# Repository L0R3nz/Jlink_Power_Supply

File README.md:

# Jlink_Power_Supply

## Project background
It's a simple project which help me in my work. I face a problem that I have to supply micro with 3V3.
J-Link allow us to supply only with 5V so I design this board to solve that problem. 

## Schematic
Schematic is very simple but if you need you can find it [here](Docs/Schematic.pdf)

## Gerber Files
Complite package ready for production you can find [here](https://github.com/L0R3nz/Jlink_Power_Supply/releases/latest)

## 3D Render

## Real photos

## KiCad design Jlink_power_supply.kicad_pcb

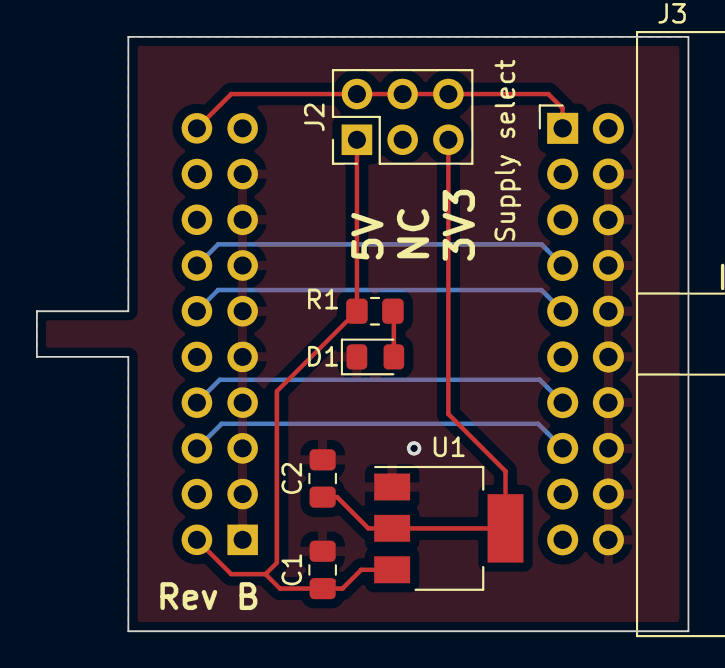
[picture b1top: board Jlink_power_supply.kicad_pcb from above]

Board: 2 copper layers, 36.2 x 33.0 mm, 8 parts (1 on the bottom side), 9 nets.

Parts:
C1, C2: 10uF; C_0805_2012Metric_Pad1.18x1.45mm_HandSolder
D1: LED_0805_2012Metric_Pad1.15x1.40mm_HandSolder
J1: Jlink input; PinSocket_2x10_P2.54mm_Horizontal
J2: Supply select; PinHeader_2x03_P2.54mm_Vertical
J3: Jlink output; IDC-Header_2x10_P2.54mm_Horizontal
R1: R_0805_2012Metric_Pad1.20x1.40mm_HandSolder
U1: AMS1117-3.3; SOT-223-3_TabPin2

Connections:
+3V3: C2.1, J2.5, U1.2 (VO)
+5V: C1.1, J1.2, J2.1, R1.2, U1.3 (VI)
GND: C1.2, C2.2, D1.1 (K), J1.1, J1.3, J1.5, J1.7, J1.9, J1.11, J1.13, J1.15, J1.17, J3.4, J3.6, J3.8, J3.10, J3.12, J3.14, J3.16, J3.18, J3.20, U1.1 (GND)
unnamed: D1.2 (A), R1.1
Reset: J1.6, J3.15
SWCLK: J1.12, J3.9
SWDIO: J1.14, J3.7
SWO: J1.8, J3.13
Vref: J1.20, J2.2, J2.4, J2.6, J3.1

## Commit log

2020-06-20 Added Ki-Cad project files
2020-06-20 Generate Gerber files ready for production
2020-06-20 Added Documentation
2020-06-20 Fix wrong path in readme file
2020-06-20 Added link to released package
2020-06-20 Added project Banner
2021-02-15 Create LICENSE
2023-03-10 Added capasitors for LDO and status led for 5V signal
